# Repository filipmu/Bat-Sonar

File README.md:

# Bat-Sonar
Bat like sonar sensor that can track multiple targets and estimate angle of arrival using chirps and cross correlation in near real time.  Code for a ARM Cortex signal processing project I completed and published on hackaday.io. 

## Video
This video shows the sensor in action.  The left graph shows the identified targets.  The size of the circles indicates the strength, and the location on the graph is their measured location.  The graph on the right shows the cross correlation signal vs distance.  The first step is pressing a switch on the board to calibrate and baseline the sensor.  Then the video shows the sensor identifying various targets.:https://vimeo.com/250041155

## How it works
The approach works natively on the 1-bit PDM output of MEMS microphones.  Since the sample rate is 4MHz, very accurate phase comparison can be done. This approach takes advantage of how the cross correlation problem simplifies when its matching a simple square wave chirp with a 1-bit PDM stream. In this case its a sum of delays with terms reflecting the signal level changes in the chirp  and delays reflecting the length of each pulse in the chirp.  This reduces the computational complexity significantly.  Note that its done in the time domain, not using the FFT as is typical with higher resolution digital samples.  The Cortex M4 has SIMD (Single Instruction Multiple Data) and DSP instructions that I carefully tuned to maximize computation speed. The theory is in this paper: :http://www.kurosawa.ip.titech.ac.jp/publications/papers/ieice08sh.pdf
 
 A much more detailed description of how it works can be found at :https://hackaday.io/project/29512-bat-sonar/details

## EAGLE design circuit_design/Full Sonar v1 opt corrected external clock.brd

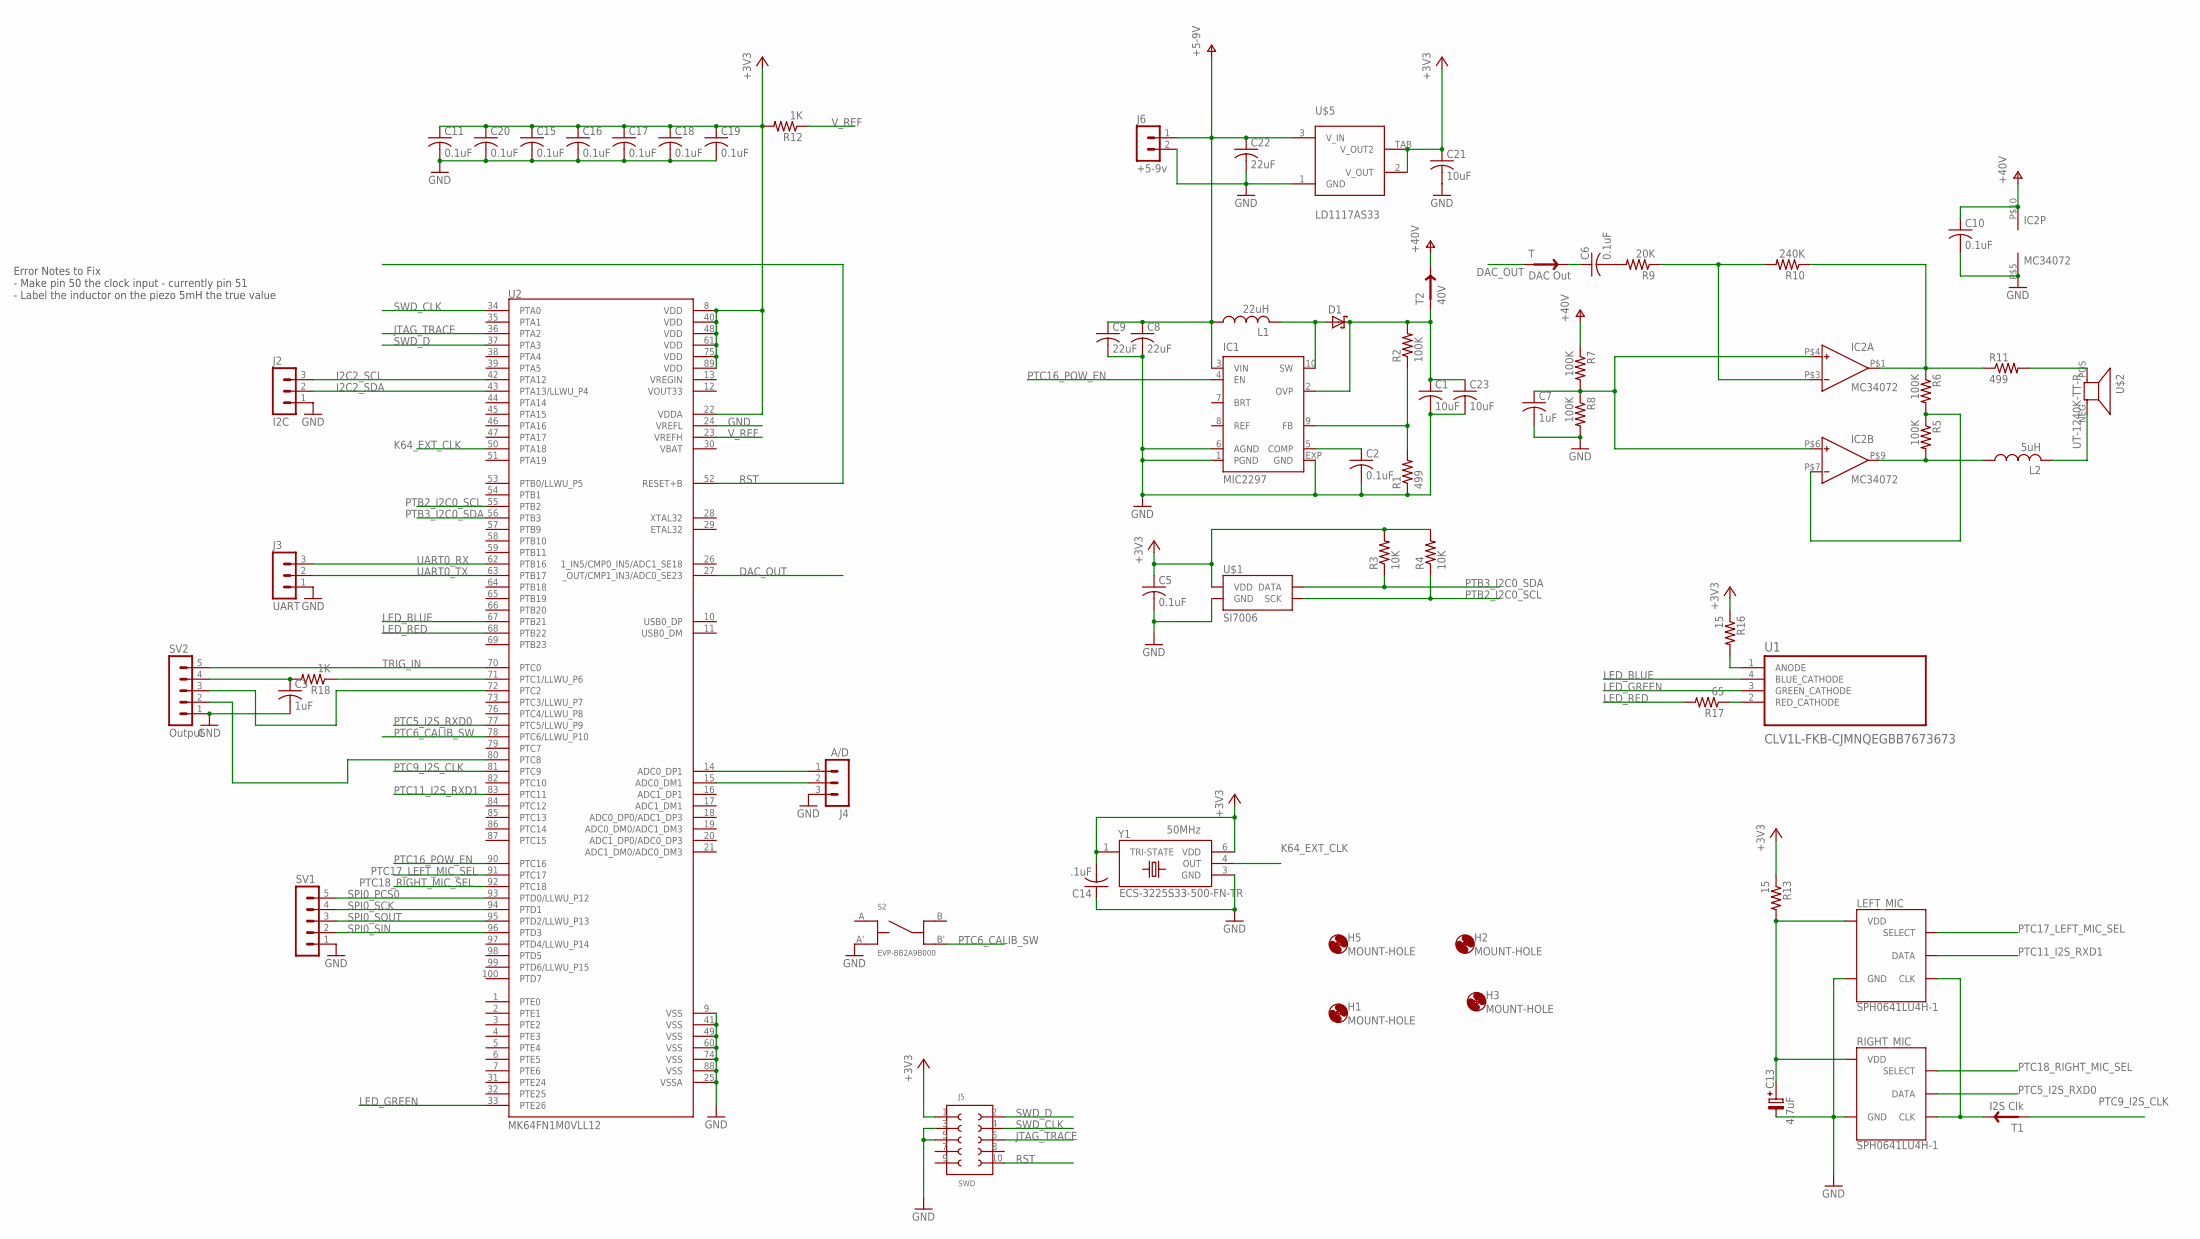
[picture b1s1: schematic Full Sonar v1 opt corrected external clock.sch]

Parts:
C1, C23: 10uF; C1206
C2, C5, C6, C10, C11, C16, C17, C18, C19: 0.1uF; C0603
C3, C7: 1uF; C0603
C8, C9, C22: 22uF; C0805
C13: 4.7uF; TE-A-3216
C14: .1uF; C0603
C15, C20: 0.1uF; C0603K
C21: 10uF; C0603
D1: DIODE_SCHOTTKYMICROSMP; DIODE_SCHOTTKY_MICROSMP
H1, H2, H3, H5: MOUNT-HOLE; SCREWHOLE2-56
IC1: MIC2297; MLF10
IC2: MC34072; WQFN10
J2: I2C; MA03-1
J3: UART; MA03-1
J4: A/D; MA03-1
J5: SWD; 62201021121
J6: +5-9v; MA02-1
L1: 22uH; INDUCTOR_BOURNS_SRN3012TA
L2: 5uH; INDUCTOR_BOURNS_SDR0503
LEFT_MIC: SPH0641LU4H-1
R1, R11: 499; R0603
R2, R5, R6, R7, R8: 100K; R0603
R3, R4: 10K; R0603
R9: 20K; R0603
R10: 240K; R0603
R12, R18: 1K; R0603
R13, R16: 15; R0603
R17: 65; R0603
RIGHT_MIC: SPH0641LU4H-1
S2: EVP-BB2A9B000; SW_EVP-BB2A9B000
SV1: MA05-1
SV2: Output; MA05-1
T: DAC Out; TESTPAD
T1: I2S Clk; TESTPAD
T2: 40V; TESTPAD
U1: CLV1L-FKB-CJMNQEGBB7673673; SOJ150P350X372-4N
U2: MK64FN1M0VLL12; QFP50P1600X1600X170-100N
U$1: SI7006
U$2: UT-1240K-TT-R
U$5: LD1117AS33; SOT223
Y1: ECS-3225S33-500-FN-TR; XTAL_ECS-3225S18-050-EN-TR

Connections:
+3V3: C5.1, C11.1, C14.2, C15.1, C16.1, C17.1, C18.1, C19.1, C20.1, C21.1, J5.1, R3.2, R4.2, R12.2, R13.1, R16.1, U2.8 (VDD), U2.22 (VDDA), U2.40 (VDD), U2.48 (VDD), U2.61 (VDD), U2.75 (VDD), U2.89 (VDD), U$1.VDD, U$5.2 (V_OUT), U$5.TAB (V_OUT2), Y1.1 (TRI-STATE), Y1.6 (VDD)
+5-9V: C8.1, C9.1, C22.1, IC1.3 (VIN), J6.1, L1.P$1 (1), U$5.3 (V_IN)
+40V: C1.1, C23.1, D1.C, IC1.2 (OVP), R2.2, T2.IN
DAC_OUT: T.IN, U2.27 (_OUT/CMP1_IN3/ADC0_SE23)
GND: C1.2, C2.2, C3.2, C5.2, C7.2, C8.2, C9.2, C10.2, C11.2, C13.-, C14.1, C15.2, C16.2, C17.2, C18.2, C19.2, C20.2, C21.2, C22.2, C23.2, IC1.1 (PGND), IC1.6 (AGND), IC1.EXP (GND), IC2.P$5 (V-), J2.1, J3.1, J4.3, J5.3 (2), J5.5 (3), J6.2, LEFT_MIC.3 (GND), R1.1, R8.2, RIGHT_MIC.3 (GND), S2.A', SV1.1, SV2.1, U2.9 (VSS), U2.24 (VREFL), U2.25 (VSSA), U2.41 (VSS), U2.49 (VSS), U2.60 (VSS), U2.74 (VSS), U2.88 (VSS), U$1.GND, U$5.1 (GND), Y1.3 (GND)
I2C2_SCL: J2.3, U2.42 (PTA12)
I2C2_SDA: J2.2, U2.43 (PTA13/LLWU_P4)
JTAG_TRACE: J5.6 (8), U2.36 (PTA2)
K64_EXT_CLK: U2.50 (PTA18), Y1.4 (OUT)
LED_BLUE: U1.4 (BLUE_CATHODE), U2.67 (PTB21)
LED_GREEN: U1.3 (GREEN_CATHODE), U2.33 (PTE26)
LED_RED: R17.2, U2.68 (PTB22)
unnamed: J4.1, U2.14 (ADC0_DP1)
unnamed: D1.A, IC1.10 (SW), L1.P$2 (2)
unnamed: J4.2, U2.15 (ADC0_DM1)
unnamed: R16.2, U1.1 (ANODE)
unnamed: C2.1, IC1.5 (COMP)
unnamed: IC2.P$9 (OUT), L2.1, R5.2
unnamed: IC2.P$7 (IN-), R5.1, R6.2
unnamed: IC2.P$1 (OUT), R6.1, R10.1, R11.1
unnamed: IC1.9 (FB), R1.2, R2.1
unnamed: R11.2, U$2.POS
unnamed: C7.1, IC2.P$4 (IN+), IC2.P$6 (IN+), R7.2, R8.1
unnamed: IC2.P$3 (IN-), R9.1, R10.2
unnamed: C6.2, R9.2
unnamed: L2.2, U$2.NEG
unnamed: C6.1, T.OUT
unnamed: LEFT_MIC.4 (CLK), RIGHT_MIC.4 (CLK), T1.OUT
unnamed: C13.+, LEFT_MIC.5 (VDD), R13.2, RIGHT_MIC.5 (VDD)
unnamed: R17.1, U1.2 (RED_CATHODE)
unnamed: R18.1, U2.71 (PTC1/LLWU_P6)
unnamed: C3.1, R18.2, SV2.4
unnamed: SV2.3, U2.72 (PTC2)
unnamed: SV2.2, U2.80 (PTC8)
PTB2_I2C0_SCL: R4.1, U2.55 (PTB2), U$1.SCK
PTB3_I2C0_SDA: R3.1, U2.56 (PTB3), U$1.DATA
PTC5_I2S_RXD0: RIGHT_MIC.1 (DATA), U2.77 (PTC5/LLWU_P9)
PTC6_CALIB_SW: S2.B', U2.78 (PTC6/LLWU_P10)
PTC9_I2S_CLK: T1.IN, U2.81 (PTC9)
PTC11_I2S_RXD1: LEFT_MIC.1 (DATA), U2.83 (PTC11)
PTC16_POW_EN: IC1.4 (EN), U2.90 (PTC16)
PTC17_LEFT_MIC_SEL: LEFT_MIC.2 (SELECT), U2.91 (PTC17)
PTC18_RIGHT_MIC_SEL: RIGHT_MIC.2 (SELECT), U2.92 (PTC18)
RST: J5.10 (6), U2.52 (RESET+B)
SPI0_PCS0: SV1.5, U2.93 (PTD0/LLWU_P12)
SPI0_SCK: SV1.4, U2.94 (PTD1)
SPI0_SIN: SV1.2, U2.96 (PTD3)
SPI0_SOUT: SV1.3, U2.95 (PTD2/LLWU_P13)
SWD_CLK: J5.4 (9), U2.34 (PTA0)
SWD_D: J5.2 (10), U2.37 (PTA3)
TRIG_IN: SV2.5, U2.70 (PTC0)
UART0_RX: J3.3, U2.62 (PTB16)
UART0_TX: J3.2, U2.63 (PTB17)
V+: C10.1, IC2.P$10 (V+), R7.1, T2.OUT
VBAT: U2.30 (VBAT)
VOUT33: U2.12 (VOUT33)
VREGIN: U2.13 (VREGIN)
V_REF: R12.1, U2.23 (VREFH)

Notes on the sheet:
50MHz
Error Notes to Fix - Make pin 50 the clock input - currently pin 51 - Label the inductor on the piezo 5mH the true value

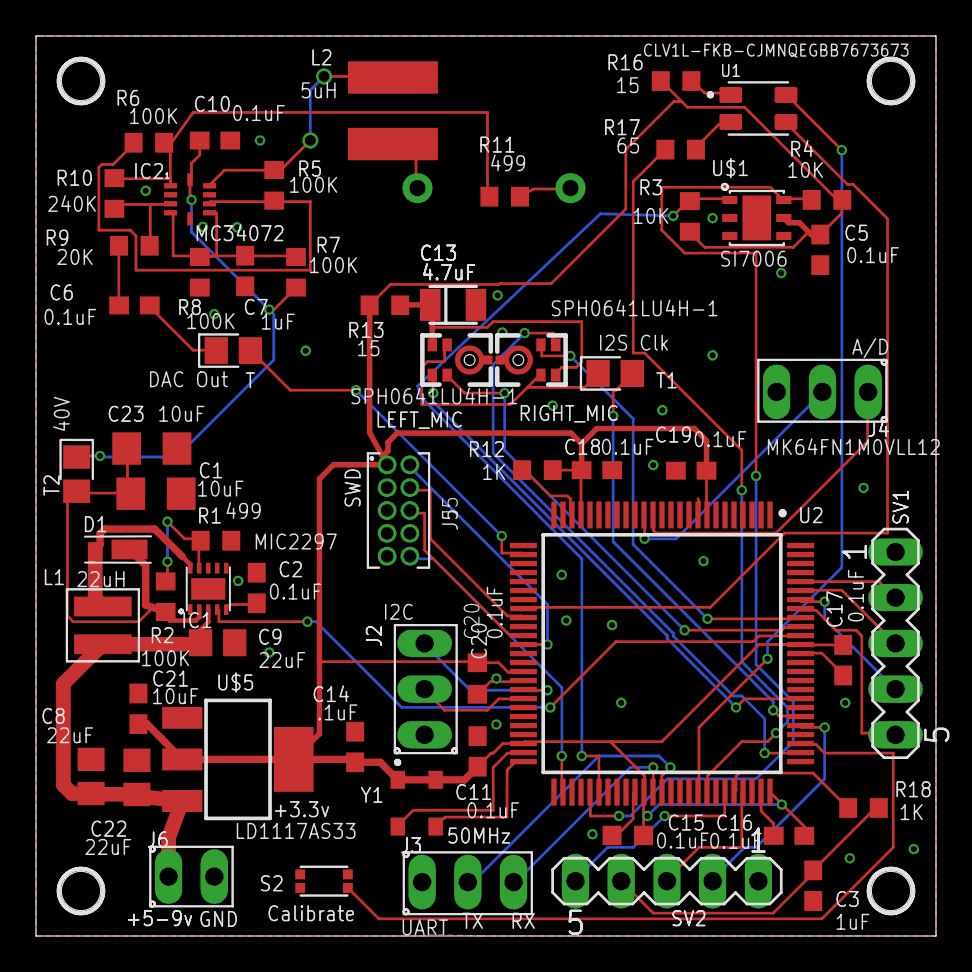
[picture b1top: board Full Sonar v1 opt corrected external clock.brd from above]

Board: 2 copper layers, 50.0 x 50.0 mm, 65 parts (1 on the bottom side), 55 nets.

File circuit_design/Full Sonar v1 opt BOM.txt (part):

Partlist exported from C:/Users/Filip/eagle/projects/Sonar/Full Sonar v1 opt.sch at 2/24/2018 7:42 AM

Qty Value                      Device                     Package                    Parts                                    Description                                                                   
1                              DIODE_SCHOTTKYMICROSMP     DIODE_SCHOTTKY_MICROSMP    D1                                       Schottky Power Rectifier                                                      
1                              MA05-1                     MA05-1                     SV1                                      PIN HEADER                                                                    
1   +5-9v                      MA02-1                     MA02-1                     J6                                                                                                                     
1   .1uF                       C-USC0603                  C0603                      C14                                      CAPACITOR, American symbol                                                    
9   0.1uF                      C-USC0603                  C0603                      C2, C5, C6, C10, C11, C16, C17, C18, C19 CAPACITOR, American symbol                                                    
2   0.1uF                      C-USC0603K                 C0603K                     C15, C20                                 CAPACITOR, American symbol                                                    
1   10                         R-US_R0603                 R0603                      R13                                      RESISTOR, American symbol                                                     
5   100K                       R-US_R0603                 R0603                      R2, R5, R6, R7, R8                       RESISTOR, American symbol                                                     
2   10K                        R-US_R0603                 R0603                      R3, R4                                   RESISTOR, American symbol                                                     
1   10uF                       C-USC0603                  C0603                      C21                                      CAPACITOR, American symbol                                                    
2   10uF                       C-USC1206                  C1206                      C1, C23                                  CAPACITOR, American symbol                                                    
1   15                         R-US_R0603                 R0603                      R16                                      RESISTOR, American symbol                                                     
2   1K                         R-US_R0603                 R0603                      R12, R18                                 RESISTOR, American symbol                                                     
2   1uF                        C-USC0603                  C0603                      C3, C7                                   CAPACITOR, American symbol                                                    
1   20K                        R-US_R0603                 R0603                      R9                                       RESISTOR, American symbol                                                     
3   22uF                       C-USC0805                  C0805                      C8, C9, C22                              CAPACITOR, American symbol                                                    
1   22uH                       INDUCTOR7                  INDUCTOR_BOURNS_SRN3012TA  L1                                                                                                                     
1   240K                       R-US_R0603                 R0603                      R10                                      RESISTOR, American symbol                                                     
1   4.7uF                      CPOLA                      TE-A-3216                  C13                                      polarized SMD caps                                                            
1   40V                        TESTPAD""                  TESTPAD                    T2                                                                                                                     
2   499                        R-US_R0603                 R0603                      R1, R11                                  RESISTOR, American symbol                                                     
1   5uH                        INDUCTOR                   INDUCTOR_BOURNS_SDR0503    L2                                                                                                                     
1   65                         R-US_R0603                 R0603                      R17                                      RESISTOR, American symbol                                                     
1   A/D                        MA03-1                     MA03-1                     J4                                       PIN HEADER                                                                    
1   CLV1L-FKB-CJMNQEGBB7673673 CLV1L-FKB-CJMNQEGBB7673673 SOJ150P350X372-4N          U1                                       None                                                                          
1   DAC Out                    TESTPAD""                  TESTPAD                    T                                                                                                                      
1   ECS-3225S33-500-FN-TR      ECS-3225S33-500-FN-TR      XTAL_ECS-3225S18-050-EN-TR Y1                                       Miniature SMD HCMOS tight stability crystal oscillator                        
1   EVP-BB2A9B000              EVP-BB2A9B000              SW_EVP-BB2A9B000           S2                                       SWITCH TACTILE SPST-NO 0.02A 15V                                              
1   I2C                        MA03-1                     MA03-1                     J2                                       PIN HEADER                                                                    
1   I2S Clk                    TESTPAD""                  TESTPAD                    T1                                                                                                                     
1   LD1117AS33                 LD1117AS33                 SOT223                     U$5                                                                                                                    
1   MC34072                    MC34072                    WQFN10                     IC2                                      Dual Precision, Low Cost, High Speed Op Amp +44v supply                       
1   MIC2297                    MIC2297                    MLF10                      IC1                                      40V PWM Boost Regulator White LED Driver                                      
1   MK64FN1M0VLL12             MK64FN1M0VLL12             QFP50P1600X1600X170-100N   U2                                       MCU 32-Bit K64F ARM Cortex M4 RISC 1MB Flash 1.8V/2.5V/3.3V 100-Pin LQFP Tray 
4   MOUNT-HOLE                 MOUNT-HOLE                 SCREWHOLE2-56              H1, H2, H3, H5                           MOUNTING HOLE with drill center marker                                        
1   Output                     MA05-1                     MA05-1                     SV2                                      PIN HEADER                                                                    
1   SI7006                     SI7006                     SI7006                     U$1                                      The Si7006 is an I2C Humidity and Temperature Sensor                          
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
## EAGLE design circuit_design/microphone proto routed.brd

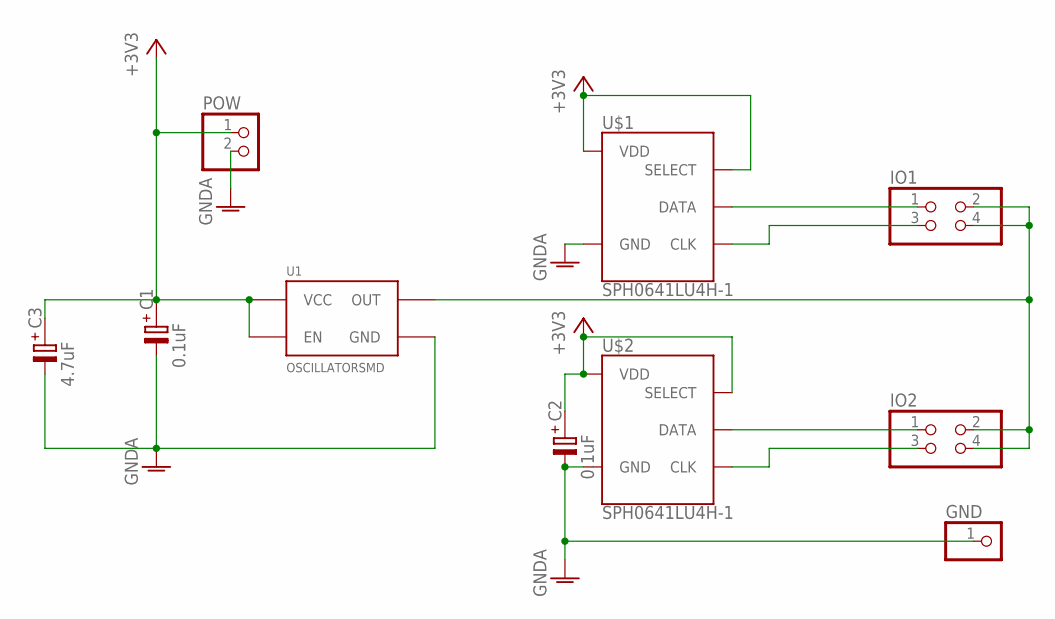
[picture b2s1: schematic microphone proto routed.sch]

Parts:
C1, C2: 0.1uF; 0805
C3: 4.7uF; TE-A-3216
GND: PINHD-1X1; 1X01
IO1, IO2: PINHD-2X2; 2X02
POW: PINHD-1X2; 1X02
U1: OSCILLATORSMD; CRYSTAL-SMD-7X5
U$1, U$2: SPH0641LU4H-1

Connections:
+3V3: C1.+, C2.+, C3.+, POW.1, U1.P$1 (EN), U1.P$4 (VCC), U$1.2 (SELECT), U$1.5 (VDD), U$2.2 (SELECT), U$2.5 (VDD)
GNDA: C1.-, C2.-, C3.-, GND.1, POW.2, U1.P$2 (GND), U$1.3 (GND), U$2.3 (GND)
unnamed: IO1.1, U$1.1 (DATA)
unnamed: IO1.3, U$1.4 (CLK)
unnamed: IO1.2, IO1.4, IO2.2, IO2.4, U1.P$3 (OUT)
unnamed: IO2.1, U$2.1 (DATA)
unnamed: IO2.3, U$2.4 (CLK)

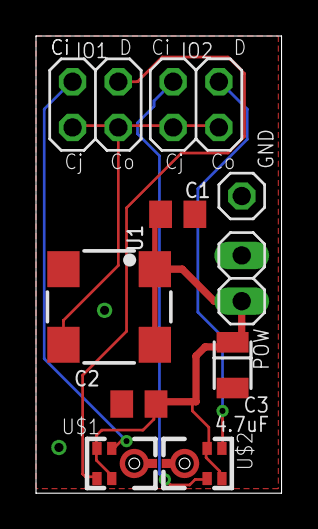
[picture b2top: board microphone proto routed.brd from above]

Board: 2 copper layers, 13.6 x 25.4 mm, 10 parts (0 on the bottom side), 7 nets.

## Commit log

2017-03-25 Initial Version - good version with 2 microphones working well
2017-04-08 put corr data in lower ram for speed increase
2017-04-27 Added a third mems input SPI0 (start does not sync with I2S) Solved issue with missing I2S bits when reading frame sizes cant be 1
2017-05-11 Tried setting up DMA, but seems to be flaky and slower. Only works when the compiler is not optimizing.
2017-05-12 test commit
2017-05-12 Removed the DMA code since it did not work. Last version has best DMA code that I could write. It was slow and did not work well at all. Not sure it would really save much time.
2017-05-12 Changed the I2S interrupt to load 5 32 bit words at a time for each channel. THis should improve performance slightly.
2017-06-03 Added support to work with octave serial communication. Sends arrays via usb serial to the Octave ap for plotting and further processing. USB serial is supported by the debugger.
2017-06-07 updated output approach to Octave to handle arbitrary sized arrays.
    shortened the size of the data sample to 1000 for quicker experiments
2017-06-22 Improved approach for serial output of arrays Made the sample length a variable that can be changed Instead of blanking for self-echos, code subtracts off the correlation when the switch SW2 on the f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
2017-07-04 Removed calc of crosscorrelation on the mems1 microphone since its not needed. This reduces calc time by about half.
    Added a calibration sequence so that when pressing SW2, it finds the
    threshold for noise (runs crosscorrelation with chirp when there is no
    output chirp) and also creates a copy of the cross correlation profile
    that is subtracted out when finding targets. This removes the
    self-echo.
    Other minor improvements
2017-07-15 Added ability to change clocks for PIT and I2S and calculate the right counts based on a chirp frequency define.
    Added ability to output the raw sound data
    Created both a baseline subtraction and blanking windows
    Changed clocks for I2S to use osc0, the 50MhZ oscilator on the board,
    which is more accurate.
2017-07-15 Changed the chirp pulse generation to be table driven. Table is updated with pulse widths. Can then have arbitrary chirp profiles calculated once.
2017-08-16 Added ability to provide a start and ending frequency in hertz for the chirp. Also chirp counter now allows more accuracy in changing frequency over the chirp length.
2018-03-09 Latest Changes
2018-05-28 Added automatic calibration after 10 pulses. Added LED support Added basic support for the custom board
2019-10-31 Improved peak detection.
2019-11-09 Scaled the image
2019-11-09 Cleaned up and posted links
